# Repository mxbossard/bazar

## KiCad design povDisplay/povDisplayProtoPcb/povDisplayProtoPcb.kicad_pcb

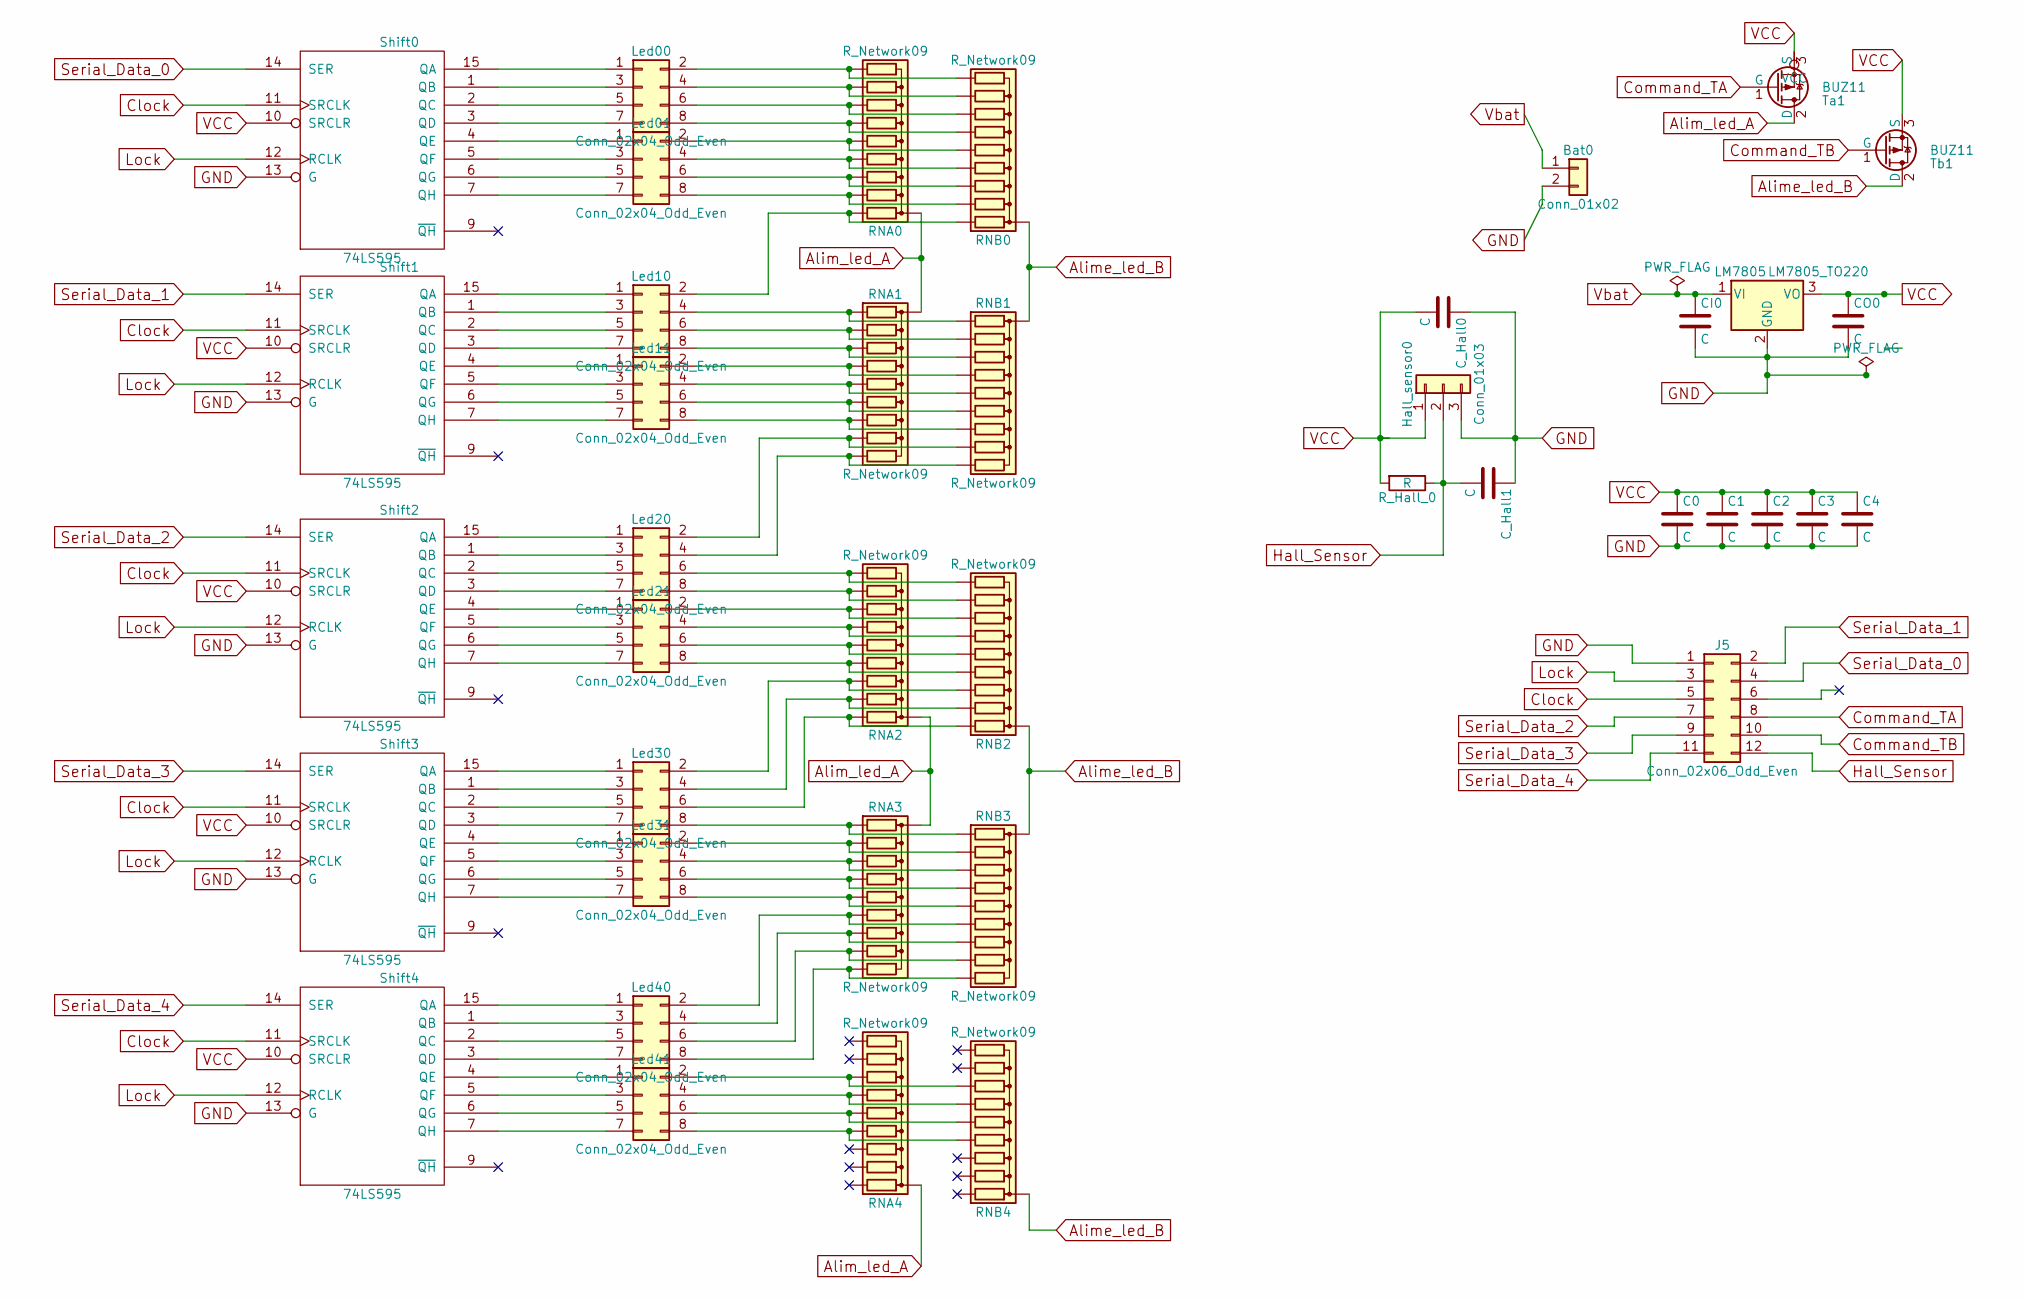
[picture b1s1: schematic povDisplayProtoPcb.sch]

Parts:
Bat0: Conn_01x02; Pin_Header_Angled_1x02_Pitch2.54mm
C0, C1, C2, C3, C4: C; C_Disc_D7.5mm_W2.5mm_P5.00mm
CI0: C; C_Rect_L4.6mm_W2.0mm_P2.50mm_MKS02_FKP02
CO0: C; C_Disc_D7.5mm_W2.5mm_P5.00mm
C_Hall0, C_Hall1: C; C_Disc_D7.5mm_W2.5mm_P5.00mm
Hall_sensor0: Conn_01x03; TO-92_Horizontal2_Inline_Narrow_Oval
J5: Conn_02x06_Odd_Even; Pin_Header_Straight_2x06_Pitch2.54mm
LM7805: LM7805_TO220; TO-220_Vertical
Led00, Led01, Led10, Led11, Led20, Led21, Led30, Led31, Led40, Led41: Conn_02x04_Odd_Even; Pin_Header_Straight_2x04_Pitch2.54mm
RNA0, RNA1, RNA2, RNA3, RNA4: R_Network09; R_Array_SIP10
RNB0, RNB1, RNB2, RNB3, RNB4: R_Network09; R_Array_SIP10
R_Hall_0: R; R_Axial_DIN0207_L6.3mm_D2.5mm_P7.62mm_Horizontal
Shift0, Shift1, Shift2, Shift3, Shift4: 74LS595; DIP-16_W7.62mm_Socket_LongPads
Ta1: BUZ11; TO-92_Horizontal2_Inline_Narrow_Oval
Tb1: BUZ11; TO-92_Horizontal2_Inline_Narrow_Oval

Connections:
Alim_led_A: RNA0.1 (common), RNA1.1 (common), RNA2.1 (common), RNA3.1 (common), RNA4.1 (common), Ta1.2 (D)
Alime_led_B: RNB0.1 (common), RNB1.1 (common), RNB2.1 (common), RNB3.1 (common), RNB4.1 (common), Tb1.2 (D)
Clock: J5.5, Shift0.11 (SRCLK), Shift1.11 (SRCLK), Shift2.11 (SRCLK), Shift3.11 (SRCLK), Shift4.11 (SRCLK)
Command_TA: J5.8, Ta1.1 (G)
Command_TB: J5.10, Tb1.1 (G)
GND: Bat0.2, C0.2, C1.2, C2.2, C3.2, C4.2, CI0.2, CO0.2, C_Hall0.1, C_Hall1.1, Hall_sensor0.3, J5.1, LM7805.2 (GND), Shift0.8 (GND), Shift0.13 (G), Shift1.8 (GND), Shift1.13 (G), Shift2.8 (GND), Shift2.13 (G), Shift3.8 (GND), Shift3.13 (G), Shift4.8 (GND), Shift4.13 (G)
Hall_Sensor: C_Hall1.2, Hall_sensor0.2, J5.12, R_Hall_0.1
Lock: J5.3, Shift0.12 (RCLK), Shift1.12 (RCLK), Shift2.12 (RCLK), Shift3.12 (RCLK), Shift4.12 (RCLK)
unnamed: Led00.1, Shift0.15 (QA)
unnamed: Led00.2, RNA0.10 (R9), RNB0.10 (R9)
unnamed: Led00.3, Shift0.1 (QB)
unnamed: Led00.4, RNA0.9 (R8), RNB0.9 (R8)
unnamed: Led00.5, Shift0.2 (QC)
unnamed: Led00.6, RNA0.8 (R7), RNB0.8 (R7)
unnamed: Led00.7, Shift0.3 (QD)
unnamed: Led00.8, RNA0.7 (R6), RNB0.7 (R6)
unnamed: Led01.1, Shift0.4 (QE)
unnamed: Led01.2, RNA0.6 (R5), RNB0.6 (R5)
unnamed: Led01.3, Shift0.5 (QF)
unnamed: Led01.4, RNA0.5 (R4), RNB0.5 (R4)
unnamed: Led01.5, Shift0.6 (QG)
unnamed: Led01.6, RNA0.4 (R3), RNB0.4 (R3)
unnamed: Led01.7, Shift0.7 (QH)
unnamed: Led01.8, RNA0.3 (R2), RNB0.3 (R2)
unnamed: Led10.1, Shift1.15 (QA)
unnamed: Led10.2, RNA0.2 (R1), RNB0.2 (R1)
unnamed: Led10.3, Shift1.1 (QB)
unnamed: Led10.4, RNA1.2 (R1), RNB1.2 (R1)
unnamed: Led10.5, Shift1.2 (QC)
unnamed: Led10.6, RNA1.3 (R2), RNB1.3 (R2)
unnamed: Led10.7, Shift1.3 (QD)
unnamed: Led10.8, RNA1.4 (R3), RNB1.4 (R3)
unnamed: Led11.1, Shift1.4 (QE)
unnamed: Led11.2, RNA1.5 (R4), RNB1.5 (R4)
unnamed: Led11.3, Shift1.5 (QF)
unnamed: Led11.4, RNA1.6 (R5), RNB1.6 (R5)
unnamed: Led11.5, Shift1.6 (QG)
unnamed: Led11.6, RNA1.7 (R6), RNB1.7 (R6)
unnamed: Led11.7, Shift1.7 (QH)
unnamed: Led11.8, RNA1.8 (R7), RNB1.8 (R7)
unnamed: Led20.1, Shift2.15 (QA)
unnamed: Led20.2, RNA1.9 (R8), RNB1.9 (R8)
unnamed: Led20.3, Shift2.1 (QB)
unnamed: Led20.4, RNA1.10 (R9), RNB1.10 (R9)
unnamed: Led20.5, Shift2.2 (QC)
unnamed: Led20.6, RNA2.10 (R9), RNB2.10 (R9)
unnamed: Led20.7, Shift2.3 (QD)
unnamed: Led20.8, RNA2.9 (R8), RNB2.9 (R8)
unnamed: Led21.1, Shift2.4 (QE)
unnamed: Led21.2, RNA2.8 (R7), RNB2.8 (R7)
unnamed: Led21.3, Shift2.5 (QF)
unnamed: Led21.4, RNA2.7 (R6), RNB2.7 (R6)
unnamed: Led21.5, Shift2.6 (QG)
unnamed: Led21.6, RNA2.6 (R5), RNB2.6 (R5)
unnamed: Led21.7, Shift2.7 (QH)
unnamed: Led21.8, RNA2.5 (R4), RNB2.5 (R4)
unnamed: Led30.1, Shift3.15 (QA)
unnamed: Led30.2, RNA2.4 (R3), RNB2.4 (R3)
unnamed: Led30.3, Shift3.1 (QB)
unnamed: Led30.4, RNA2.3 (R2), RNB2.3 (R2)
unnamed: Led30.5, Shift3.2 (QC)
unnamed: Led30.6, RNA2.2 (R1), RNB2.2 (R1)
unnamed: Led30.7, Shift3.3 (QD)
unnamed: Led30.8, RNA3.2 (R1), RNB3.2 (R1)
unnamed: Led31.1, Shift3.4 (QE)
unnamed: Led31.2, RNA3.3 (R2), RNB3.3 (R2)
unnamed: Led31.3, Shift3.5 (QF)
unnamed: Led31.4, RNA3.4 (R3), RNB3.4 (R3)
unnamed: Led31.5, Shift3.6 (QG)
unnamed: Led31.6, RNA3.5 (R4), RNB3.5 (R4)
unnamed: Led31.7, Shift3.7 (QH)
unnamed: Led31.8, RNA3.6 (R5), RNB3.6 (R5)
unnamed: Led40.1, Shift4.15 (QA)
unnamed: Led40.2, RNA3.7 (R6), RNB3.7 (R6)
unnamed: Led40.3, Shift4.1 (QB)
unnamed: Led40.4, RNA3.8 (R7), RNB3.8 (R7)
unnamed: Led40.5, Shift4.2 (QC)
unnamed: Led40.6, RNA3.9 (R8), RNB3.9 (R8)
unnamed: Led40.7, Shift4.3 (QD)
unnamed: Led40.8, RNA3.10 (R9), RNB3.10 (R9)
unnamed: Led41.1, Shift4.4 (QE)
unnamed: Led41.2, RNA4.8 (R7), RNB4.8 (R7)
unnamed: Led41.3, Shift4.5 (QF)
unnamed: Led41.4, RNA4.7 (R6), RNB4.7 (R6)
unnamed: Led41.5, Shift4.6 (QG)
unnamed: Led41.6, RNA4.6 (R5), RNB4.6 (R5)
unnamed: Led41.7, Shift4.7 (QH)
unnamed: Led41.8, RNA4.5 (R4), RNB4.5 (R4)
Serial_Data_0: J5.4, Shift0.14 (SER)
Serial_Data_1: J5.2, Shift1.14 (SER)
Serial_Data_2: J5.7, Shift2.14 (SER)
Serial_Data_3: J5.9, Shift3.14 (SER)
Serial_Data_4: J5.11, Shift4.14 (SER)
VCC: C0.1, C1.1, C2.1, C3.1, C4.1, CO0.1, C_Hall0.2, Hall_sensor0.1, LM7805.3 (VO), R_Hall_0.2, Shift0.10 (SRCLR), Shift0.16 (VCC), Shift1.10 (SRCLR), Shift1.16 (VCC), Shift2.10 (SRCLR), Shift2.16 (VCC), Shift3.10 (SRCLR), Shift3.16 (VCC), Shift4.10 (SRCLR), Shift4.16 (VCC), Ta1.3 (S), Tb1.3 (S)
Vbat: Bat0.1, CI0.1, LM7805.1 (VI)

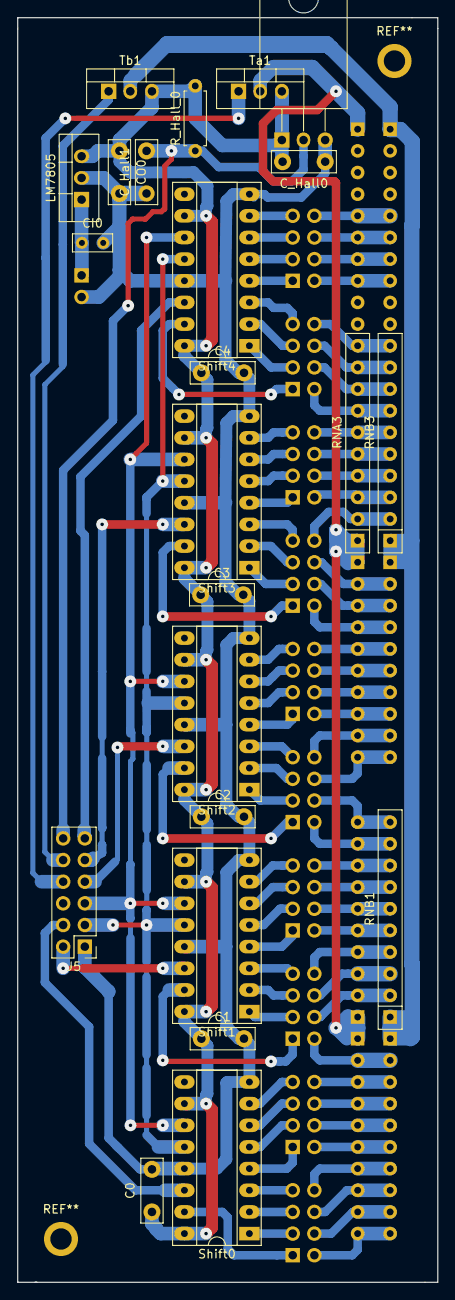
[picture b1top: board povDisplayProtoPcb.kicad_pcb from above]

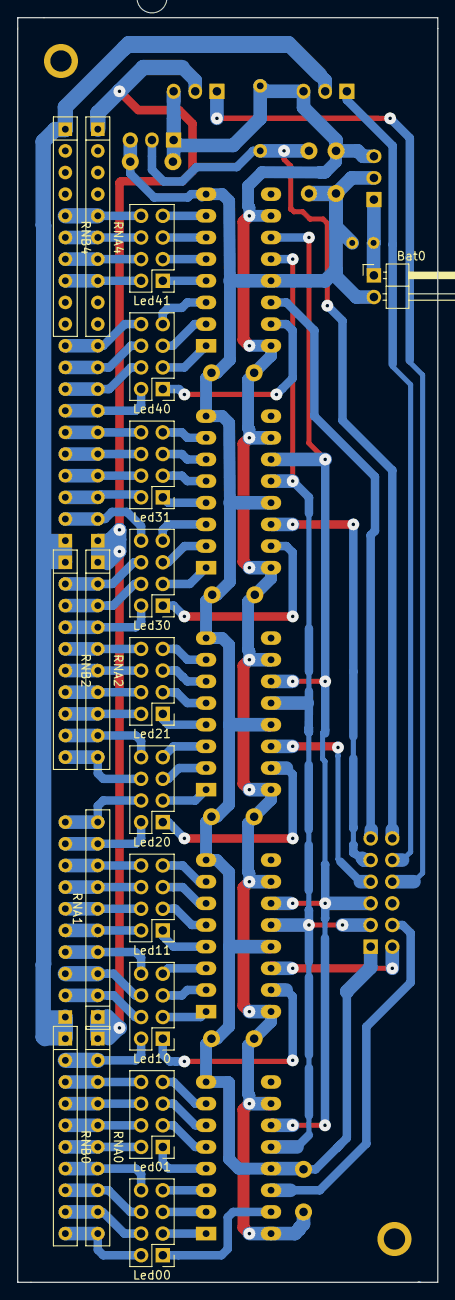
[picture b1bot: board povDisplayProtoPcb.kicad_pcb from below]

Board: 4 copper layers, 49.3 x 148.3 mm, 41 parts (18 on the bottom side), 95 nets.

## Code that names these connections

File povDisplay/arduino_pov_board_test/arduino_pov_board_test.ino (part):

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

// PINS are expressed in "Arduino value"
const int HALL_SENSOR_PIN = 3; // Attention ici on utilise le pin arduino uno 3

const int A_COMMAND_PIN = 4;
const int B_COMMAND_PIN = 5;

const int CLOCK_PIN = 13;
const int LOCK_PIN = 6;

const int SERIAL_DATA_0_PIN = 8;
const int SERIAL_DATA_1_PIN = 9;
const int SERIAL_DATA_2_PIN = 10;
const int SERIAL_DATA_3_PIN = 11;
const int SERIAL_DATA_4_PIN = 12;
const int SERIAL_DATA_PINS[SERIAL_LATCH_COUNT] = {SERIAL_DATA_0_PIN, SERIAL_DATA_1_PIN, SERIAL_DATA_2_PIN, SERIAL_DATA_3_PIN, SERIAL_DATA_4_PIN};

const byte OFF_CURRENT = 0;
const byte MIN_CURRENT = 1;
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  digitalWrite(B_COMMAND_PIN, HIGH);
  
  digitalWrite(CLOCK_PIN, LOW);
  digitalWrite(LOCK_PIN, LOW);

  // Config outputs
  pinMode(A_COMMAND_PIN, OUTPUT);
  pinMode(B_COMMAND_PIN, OUTPUT);
  
  pinMode(CLOCK_PIN, OUTPUT);
  pinMode(LOCK_PIN, OUTPUT);
  
  for(int k = 0; k < SERIAL_LATCH_COUNT; k ++) {
    pinMode(SERIAL_DATA_PINS[k], OUTPUT);
  }
  
  // Config inputs
  pinMode(HALL_SENSOR_PIN, INPUT_PULLUP);
  
  // Config interrupts
  #if INTERUPT_ON_HALL_DETECTION == 1
  attachInterrupt(HALL_SENSOR_PIN - 2, hallDisplayInterrupt, RISING); // I should use digitalPinToInterrupt(), but where is it declared ?
  #endif

  /* This config break de delay().
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  #endif
  
  // Lock on rising edge
  digitalWrite(LOCK_PIN, LOW);
    
  #if SLOW_DISPLAY_DRIVING_CLOCK == 1
  delay(1);
  #endif
  
  digitalWrite(LOCK_PIN, HIGH);
}

// Send one complete byte of information on a serial latch
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
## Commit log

2018-03-04 First work on a pov display simulator.
2018-03-06 Accelerate by precalculating all circles and image samples. Now use a led scheme to add more flexibility with the led arrangements.
2018-03-10 Fix RGB colors, try to improve display performance.
2018-03-15 Work on pcb.
2018-03-15 Add cutting edge.
2018-03-16 Fix drill output.
2018-03-22 Add mounting holes
2018-04-06 Add a first arduino sketch to test the proto pov board.
2018-04-10 Add work on arduino test sketch and stator svg design.
2018-04-12 Add rotor design plus a cut test board to test the lasert cut kerf.
2018-04-12 Update stator design with adjustement from cutting test board.
2018-04-12 Adjust rotor design.
2018-04-12 Fix shifting and memcpy buggy.
2018-04-28 A lot of works on arduino test sketch. Timers are working.
2018-04-30 Work on Pictures storage and readings.
2018-05-01 Reduce clock cycles need on all key functions.
2018-05-01 Add options to script and add a feature: built transposed binary data from what is previsualised for the pov display.
2018-05-01 First working version !
2018-05-08 Add board tests to troobleshot problems.
2018-05-08 draw a new rotor with a better equilibrium.
2018-10-20 Add semaphore initial works.
2018-10-20 Work on semaphore arms to build a dxf.
2018-10-21 Works on 3D semaphores arms.
2018-10-25 Add clamping holes to 3D arms.
2018-10-25 Add some pieces to test 2 bearings on regulator.
2018-10-27 Add 108 frig holder scad.
2018-10-27 Add work on buck converter.
2018-10-27 Add work on saving the old labomedia wiki.
2018-10-27 Last work on pov display.
2018-10-27 Adjustments on 108 fridge holder.
2018-10-29 Minor customizing.
2019-01-21 Add a script to verify old wiki redirected URLs.
2019-01-23 Document what actions need to be done.
2019-02-23 Add initial work on v2 semaphore.
2019-02-24 Minor adjustment following 3D printing calibration.
2019-02-25 Modify indicator surronding to add a second bearing. Attempt to reduce to 28 teeth.
2019-02-27 Modify semaphore arrangement to put bearings on regulateur.
2019-02-28 Add new pulley indicator v3 for bearings on regulator design.
2019-03-01 Adjust parameters after a some prints.
2019-03-02 Add a first mat.
2019-03-02 Add mat head with fixation holes
2019-03-02 Add a first semaphore mat holder.
2019-03-02 Add a first nema17 mount.
2019-03-02 Add shaft hole to nema17 mount..
2019-03-03 Modify nema17 mount to reduce width.
2019-03-03 Modify mat to be constitued of multiple layers. Reduce logo size and add some 3d effect.
2019-03-09 Add design gears for proto v2.
2019-03-09 Add missing scad files.
2019-03-09 Add arduino motor test sketches.
2019-03-10 Add test design to mount nema17 on mat and add a wood cut to test gears.
2019-03-10 Adjust motor shaft hole diameter.
2019-03-10 Add code to play chappe alphabet with different transition algorithm.
2019-03-10 minor fixes.
2019-03-14 Add modifications for semaphore proto v2.
2019-03-20 Add some bridge length in between pulleys.
2019-03-21 Reorg semaphore v2 and add mat_ends to cut.
2019-04-04 Add work on turbin test bench for the small windturbin.
2019-11-06 Add mqtt works with python.
2019-11-09 Add a script which scrape smartcitizen data and push it to a MQTT broker.
2020-12-29 LEDs blinking simulation tests.
2020-12-29 Variabilise MQTT host and topic.
2020-12-29 Work on a JS crwaler ?
2020-12-30 Add parametric screen size.
2020-12-30 Rename ledSimulations project.
2022-03-10 Modelisations de meubles.
2023-03-30 Add bessey protective pads 3d model.
2023-03-30 Add mode and text.
2023-03-30 Tunning of params.
